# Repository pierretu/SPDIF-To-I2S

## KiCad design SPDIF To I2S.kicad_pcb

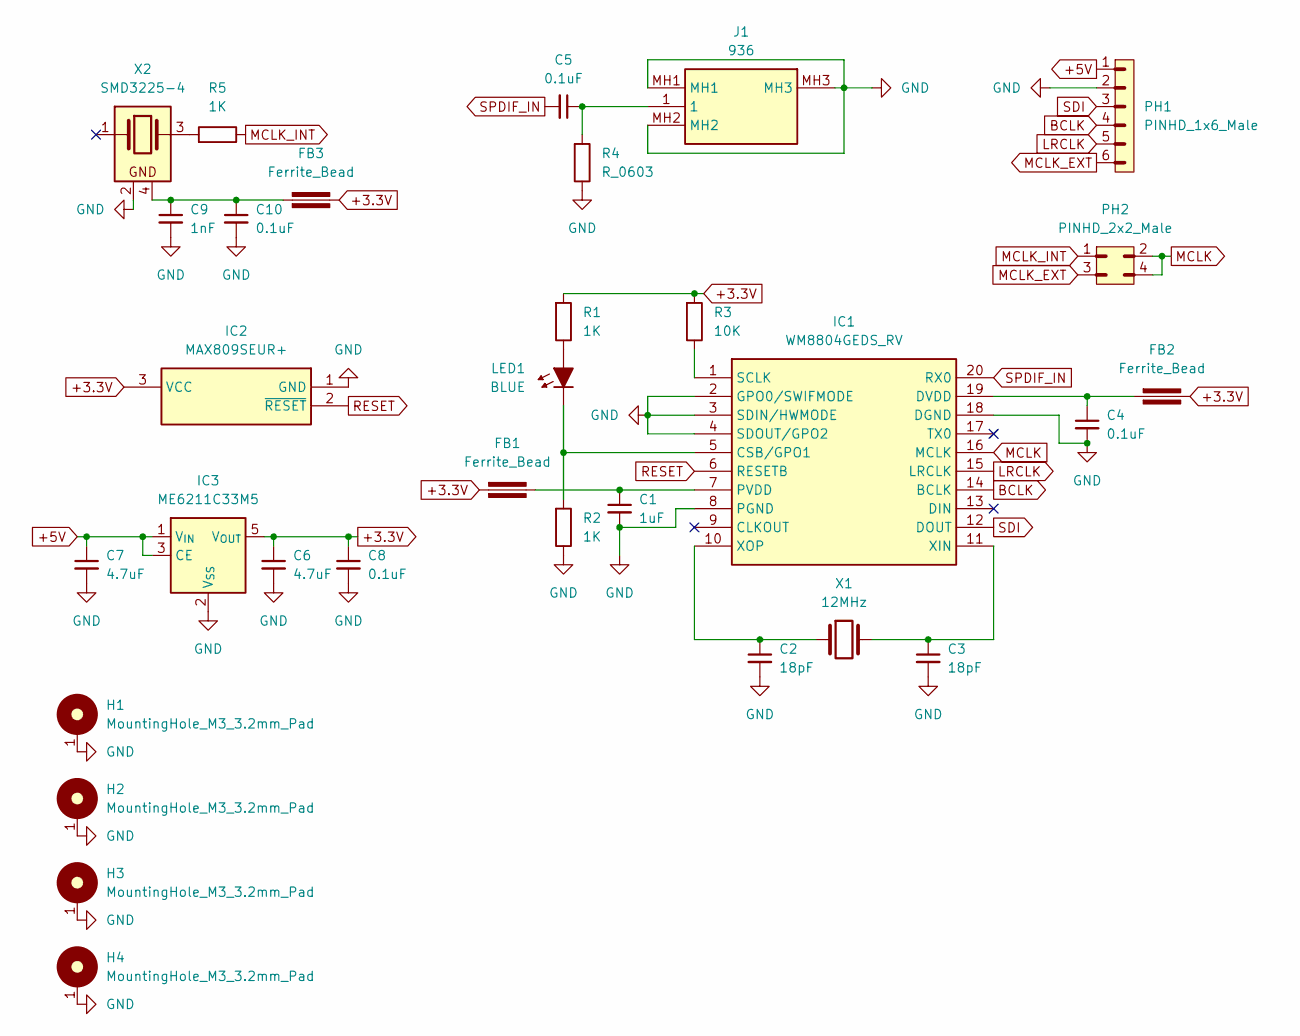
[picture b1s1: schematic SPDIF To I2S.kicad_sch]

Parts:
C1: 1uF_0603_25V; C_0603_1608Metric; Part Number GRM188R61E105KA12D; JLCPCB ID C15849
C2: 18pF/50V; C_0603_1608Metric; Part Number C0603C180J5GACTU; JLCPCB ID C1647
C3: 18pF_0603_50V; C_0603_1608Metric; Part Number C0603C180J5GACTU; JLCPCB ID C1647
C4, C5, C8, C10: 0.1uF_0603_16V; C_0603_1608Metric; Part Number 0603YC104KAT2A; JLCPCB ID C14663
C6, C7: 4.7uF_1206_lowESR; C_0603_1608Metric; Part Number EMF316AB7475KLHT
C9: 1nF_0603_50V; C_0603_1608Metric; Part Number GRM1885C1H102JA01D; JLCPCB ID C163508
FB1, FB2, FB3: Ferrite_Bead; Fuse_0603_1608Metric
H1, H2, H3, H4: MountingHole_M3_3.2mm_Pad; MountingHole_3.2mm_Pad
IC1: WM8804GEDS_RV; SOP65P780X200-20N; Manufacturer_Part_Number WM8804GEDS/RV
IC2: MAX809SEUR+; SOT95P237X112-3N; Manufacturer_Part_Number MAX809SEUR+
IC3: ME6211C33M5; SOT-23-5
J1: 936; Manufacturer_Part_Number 936
LED1: BLUE; LED_0603_1608Metric
PH1: PINHD_1x6_Male; PinHeader_1x06_P2.54mm_Vertical
PH2: PINHD_2x2_Male; PinHeader_2x02_P2.54mm_Vertical
R1, R2, R5: 1K; R_0603_1608Metric
R3: 10K; R_0603_1608Metric
R4: R_0603; R_0603_1608Metric
X1: 12MHz; Crystal_HC18-U_Vertical
X2: SMD3225-4; Crystal_SMD_3225-4Pin_3.2x2.5mm

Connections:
+3.3V: C6.1, C8.1, FB1.1, FB2.2, FB3.2, IC2.3 (VCC), IC3.5 (V_{OUT}), R1.1, R3.1
+5V: C7.1, IC3.1 (V_{IN}), IC3.3 (CE), PH1.1
BCLK: IC1.14 (BCLK), PH1.4
GND: C1.2, C2.2, C3.2, C4.2, C6.2, C7.2, C8.2, C9.2, C10.2, H1.1, H2.1, H3.1, H4.1, IC1.2 (GPO0/SWIFMODE), IC1.3 (SDIN/HWMODE), IC1.4 (SDOUT/GPO2), IC1.8 (PGND), IC1.18 (DGND), IC2.1 (GND), IC3.2 (V_{SS}), J1.MH1, J1.MH2, J1.MH3, PH1.2, R2.2, R4.2, X2.2 (GND)
LRCLK: IC1.15 (LRCLK), PH1.5
MCLK: IC1.16 (MCLK), PH2.2, PH2.4
MCLK_EXT: PH1.6, PH2.3
MCLK_INT: PH2.1, R5.2
unnamed: C5.1, J1.1, R4.1
unnamed: IC1.5 (CSB/GPO1), LED1.1 (K), R2.1
unnamed: C4.1, FB2.1, IC1.19 (DVDD)
unnamed: C1.1, FB1.2, IC1.7 (PVDD)
unnamed: IC1.1 (SCLK), R3.2
unnamed: C3.1, IC1.11 (XIN), X1.2
unnamed: C2.1, IC1.10 (XOP), X1.1
unnamed: LED1.2 (A), R1.2
unnamed: R5.1, X2.3 (OUT)
unnamed: C9.1, C10.1, FB3.1, X2.4 (VDD)
RESET: IC1.6 (RESETB), IC2.2 (~RESET)
SDI: IC1.12 (DOUT), PH1.3
SPDIF_IN: C5.2, IC1.20 (RX0)

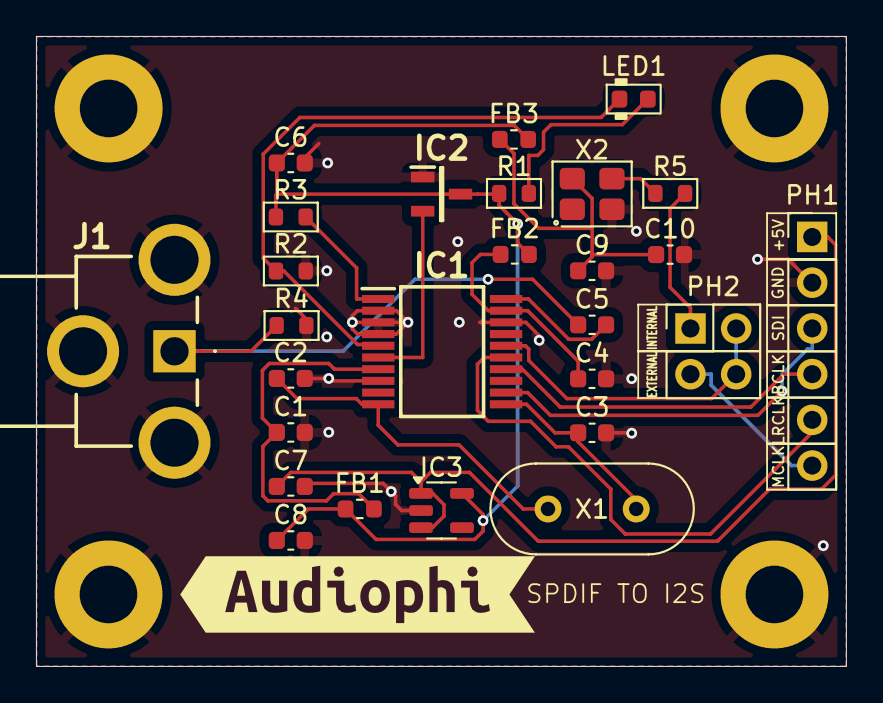
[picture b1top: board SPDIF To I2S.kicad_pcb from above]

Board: 2 copper layers, 45.0 x 35.0 mm, 32 parts (0 on the bottom side), 21 nets.

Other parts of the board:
kibuzzard-67581894: G***; kibuzzard-67581894

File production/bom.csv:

Designator,Footprint,Quantity,Value,LCSC Part #
C1,0603,1,1uF_0603_25V,
"C10, C4, C5, C8",0603,4,0.1uF_0603_16V,
C2,0603,1,18pF/50V,
C3,0603,1,18pF_0603_50V,
"C6, C7",0603,2,4.7uF_1206_lowESR,
C9,0603,1,1nF_0603_50V,
"FB1, FB2, FB3",0603,3,Ferrite_Bead,
"H1, H2, H3, H4",MountingHole_3.2mm_Pad,4,MountingHole_M3_3.2mm_Pad,
IC1,SOP65P780X200-20N,1,WM8804GEDS_RV,
IC2,SOT95P237X112-3N,1,MAX809SEUR+,
IC3,SOT-23-5,1,ME6211C33M5,
J1,936,1,936,
LED1,0603,1,BLUE,
PH1,PinHeader_1x06_P2.54mm_Vertical,1,PINHD_1x6_Male,
PH2,PinHeader_2x02_P2.54mm_Vertical,1,PINHD_2x2_Male,
"R1, R2, R5",0603,3,1K,
R3,0603,1,10K,
R4,0603,1,R_0603,
X1,Crystal_HC18-U_Vertical,1,12MHz,
X2,Crystal_SMD_3225-4Pin_3.2x2.5mm,1,SMD3225-4,
